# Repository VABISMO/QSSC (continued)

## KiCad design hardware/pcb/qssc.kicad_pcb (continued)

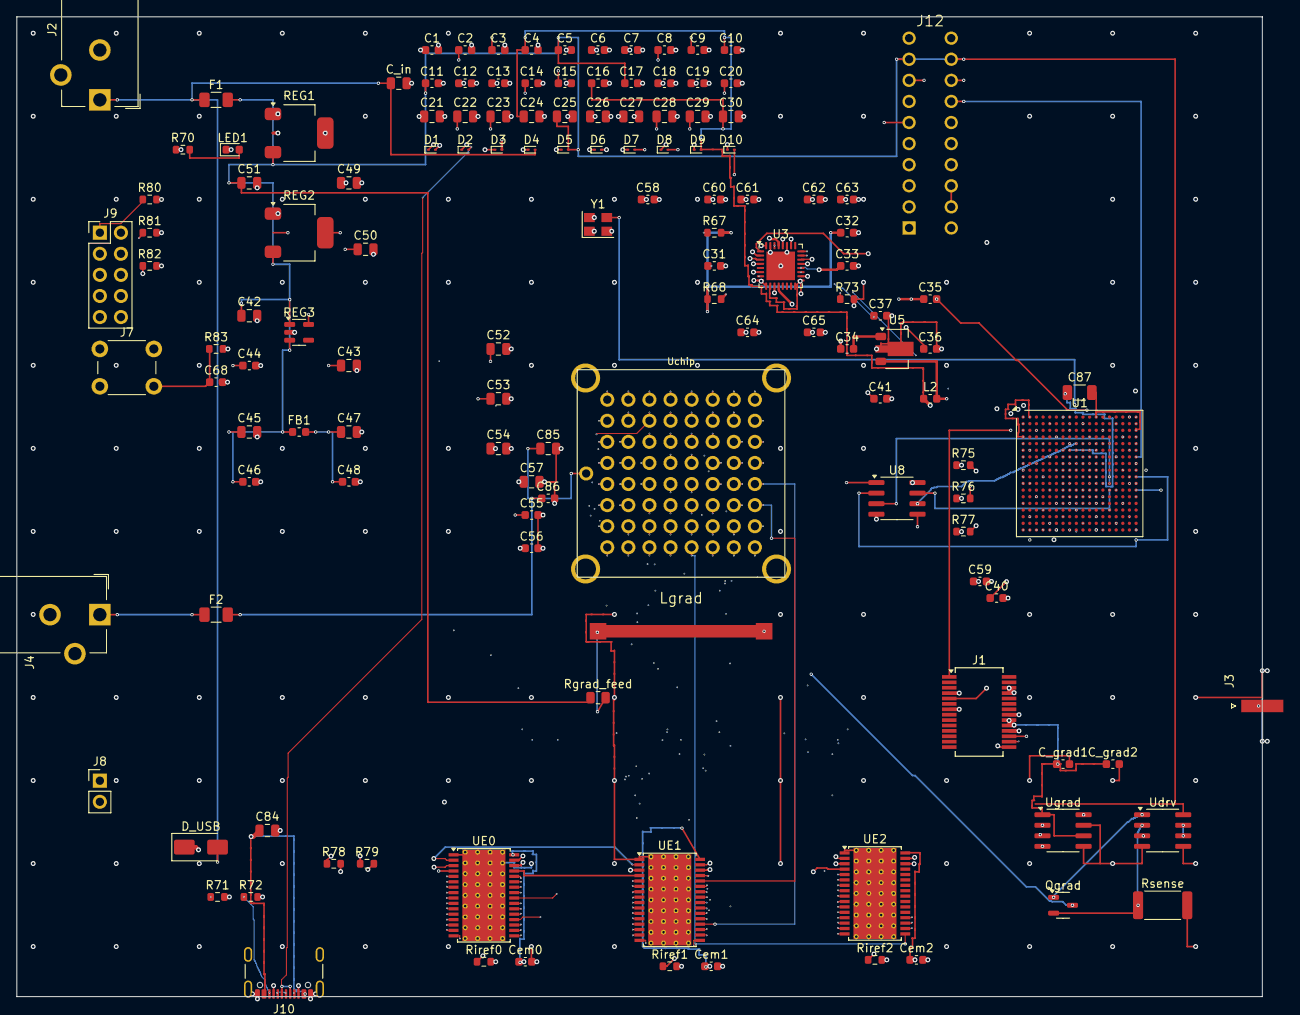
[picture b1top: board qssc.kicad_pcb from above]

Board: 6 copper layers, 150.0 x 118.0 mm, 135 parts (0 on the bottom side), 144 nets.

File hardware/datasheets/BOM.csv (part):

Board,Designators,Qty,Value,Footprint,Manufacturer,MPN,DatasheetURL
main,"C36, C37, C41",3,100n,Capacitor_SMD:C_0603_1608Metric,,,
grad,"C36, C37, C41",3,100n,Capacitor_SMD:C_0603_1608Metric,,,
main,"C1, C2, C3, C4, C5, C6, C7, C8, C9, C10, C11, C12, C13, C14, C15, C16, C17, C18, C19, C20, C40, C44, C46, C48, C55, C56, C58, C59, C60, C61, C62, C63, C64, C65, C68, C86, Cem0, Cem1, Cem2",39,100nF,Capacitor_SMD:C_0603_1608Metric,,,
grad,"C_grad1, C_grad2, C1, C2, C3, C4, C5, C6, C7, C8, C9, C10, C11, C12, C13, C14, C15, C16, C17, C18, C19, C20, C40, C44, C46, C48, C55, C56, C58, C59, C60, C61, C62, C63, C64, C65, C68, C86, Cem0, Cem1, Cem2",41,100nF,Capacitor_SMD:C_0603_1608Metric,,,
main,L2,1,100nH,Inductor_SMD:L_0603_1608Metric,,,
grad,L2,1,100nH,Inductor_SMD:L_0603_1608Metric,,,
main,"C34, C35",2,100p,Capacitor_SMD:C_0603_1608Metric,,,
grad,"C34, C35",2,100p,Capacitor_SMD:C_0603_1608Metric,,,
main,R83,1,10k,Resistor_SMD:R_0603_1608Metric,,,
grad,R83,1,10k,Resistor_SMD:R_0603_1608Metric,,,
main,C32,1,10n,Capacitor_SMD:C_0603_1608Metric,,,
grad,C32,1,10n,Capacitor_SMD:C_0603_1608Metric,,,
main,R67,1,1k,Resistor_SMD:R_0603_1608Metric,,,
grad,R67,1,1k,Resistor_SMD:R_0603_1608Metric,,,
main,R68,1,2.2k,Resistor_SMD:R_0603_1608Metric,,,
grad,R68,1,2.2k,Resistor_SMD:R_0603_1608Metric,,,
main,"C31, C33",2,220p,Capacitor_SMD:C_0603_1608Metric,,,
grad,"C31, C33",2,220p,Capacitor_SMD:C_0603_1608Metric,,,
main,"C49, C50, C85",3,22uF,Capacitor_SMD:C_0805_2012Metric,,,
grad,"C49, C50, C85",3,22uF,Capacitor_SMD:C_0805_2012Metric,,,
main,"R78, R79",2,27R,Resistor_SMD:R_0603_1608Metric,,,
grad,"R78, R79",2,27R,Resistor_SMD:R_0603_1608Metric,,,
main,R70,1,330,Resistor_SMD:R_0603_1608Metric,,,
grad,R70,1,330,Resistor_SMD:R_0603_1608Metric,,,
main,"R73, R75, R76, R77, R80, R81, R82",7,4.7k,Resistor_SMD:R_0603_1608Metric,,,
grad,"R73, R75, R76, R77, R80, R81, R82",7,4.7k,Resistor_SMD:R_0603_1608Metric,,,
main,"C52, C53, C54, C57, C84",5,4.7uF,Capacitor_SMD:C_0805_2012Metric,,,
grad,"C52, C53, C54, C57, C84",5,4.7uF,Capacitor_SMD:C_0805_2012Metric,,,
main,C87,1,47uF,Capacitor_SMD:C_1206_3216Metric,,,
grad,C87,1,47uF,Capacitor_SMD:C_1206_3216Metric,,,
main,"R71, R72",2,5.1k,Resistor_SMD:R_0603_1608Metric,,,
grad,"R71, R72",2,5.1k,Resistor_SMD:R_0603_1608Metric,,,
main,"D1, D2, D3, D4, D5, D6, D7, D8, D9, D10",10,ESD5V0,Diode_SMD:D_SOD-923,ON Semi,ESD5V0S3B-U,https://www.onsemi.com/pub/Collateral/ESD5V0S3B-U-D.PDF
grad,"D1, D2, D3, D4, D5, D6, D7, D8, D9, D10",10,ESD5V0,Diode_SMD:D_SOD-923,ON Semi,ESD5V0S3B-U,https://www.onsemi.com/pub/Collateral/ESD5V0S3B-U-D.PDF
grad,Rgrad_feed,1,0R,Resistor_SMD:R_0805_2012Metric,,,
grad,Rsense,1,1,Resistor_SMD:R_2512_6332Metric,,,
main,Y1,1,100MHz XO,Oscillator:Oscillator_SMD_Abracon_ASE-4Pin_3.2x2.5mm,Abracon,ASE-100.000MHZ-LR,https://abracon.com/Oscillators/ASE.pdf
grad,Y1,1,100MHz XO,Oscillator:Oscillator_SMD_Abracon_ASE-4Pin_3.2x2.5mm,Abracon,ASE-100.000MHZ-LR,https://abracon.com/Oscillators/ASE.pdf
head,"C_ahf, Cref, Crio0, Crio1, Crio2, Crio3, Cua0, Cua1, Cua2, Cua3, Cud0, Cud1, Cud2, Cud3, Cur0, Cur1, Cur2, Cur3, Cut0, Cut1, Cut2, Cut3, Cut4, Cut5, Cut6, Cut7, Cut8, Cut9, Cut10, Cut11, Cut12, Cut13, Cut14, Cut15",34,100nF,Capacitor_SMD:C_0603_1608Metric,,,
head,"Rref1, Rref2",2,10k,Resistor_SMD:R_0603_1608Metric,,,
main,"C_in, C21, C22, C23, C24, C25, C26, C27, C28, C29, C30, C42, C43, C45, C47, C51",16,10uF,Capacitor_SMD:C_0805_2012Metric,,,
head,"C_5V, C_Abulk, CuaB0, CuaB1, CuaB2, CuaB3",6,10uF,Capacitor_SMD:C_0805_2012Metric,,,
grad,"C_in, C21, C22, C23, C24, C25, C26, C27, C28, C29, C30, C42, C43, C45, C47, C51",16,10uF,Capacitor_SMD:C_0805_2012Metric,,,
main,J4,1,12V LED,Connector_BarrelJack:BarrelJack_CUI_PJ-102AH_Horizontal,CUI,PJ-102AH,https://www.cui.com/product/resource/pj-102a.pdf
grad,J4,1,12V LED,Connector_BarrelJack:BarrelJack_CUI_PJ-102AH_Horizontal,CUI,PJ-102AH,https://www.cui.com/product/resource/pj-102a.pdf
main,F2,1,1A PTC,Fuse:Fuse_1206_3216Metric,,,
grad,F2,1,1A PTC,Fuse:Fuse_1206_3216Metric,,,
head,"Rf0, Rf1, Rf2, Rf3, Rf4, Rf5, Rf6, Rf7, Rf8, Rf9, Rf10, Rf11, Rf12, Rf13, Rf14, Rf15, Rf16, Rf17, Rf18, Rf19, Rf20, Rf21, Rf22, Rf23, Rf24, Rf25, Rf26, Rf27, Rf28, Rf29, Rf30, Rf31, Rf32, Rf33, Rf34, Rf35, Rf36, Rf37, Rf38, Rf39, Rf40, Rf41, Rf42, Rf43, Rf44, Rf45, Rf46, Rf47, Rf48, Rf49, Rf50, Rf51, Rf52, Rf53, Rf54, Rf55, Rf56, Rf57, Rf58, Rf59, Rf60, Rf61, Rf62, Rf63",64,1M,Resistor_SMD:R_0603_1608Metric,,,
head,"Cf0, Cf1, Cf2, Cf3, Cf4, Cf5, Cf6, Cf7, Cf8, Cf9, Cf10, Cf11, Cf12, Cf13, Cf14, Cf15, Cf16, Cf17, Cf18, Cf19, Cf20, Cf21, Cf22, Cf23, Cf24, Cf25, Cf26, Cf27, Cf28, Cf29, Cf30, Cf31, Cf32, Cf33, Cf34, Cf35, Cf36, Cf37, Cf38, Cf39, Cf40, Cf41, Cf42, Cf43, Cf44, Cf45, Cf46, Cf47, Cf48, Cf49, Cf50, Cf51, Cf52, Cf53, Cf54, Cf55, Cf56, Cf57, Cf58, Cf59, Cf60, Cf61, Cf62, Cf63",64,1pF,Capacitor_SMD:C_0603_1608Metric,,,
head,"Crgc0, Crgc1, Crgc2, Crgc3, Crgd0, Crgd1, Crgd2, Crgd3",8,1uF,Capacitor_SMD:C_0603_1608Metric,,,
main,F1,1,2A PTC,Fuse:Fuse_1206_3216Metric,Littelfuse,nanoSMDC020F,https://www.littelfuse.com/media?resourcetype=datasheets&val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
grad,F1,1,2A PTC,Fuse:Fuse_1206_3216Metric,Littelfuse,nanoSMDC020F,https://www.littelfuse.com/media?resourcetype=datasheets&val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
main,"Riref0, Riref1, Riref2",3,4.87k,Resistor_SMD:R_0603_1608Metric,,,
grad,"Riref0, Riref1, Riref2",3,4.87k,Resistor_SMD:R_0603_1608Metric,,,
main,J2,1,5V Barrel,Connector_BarrelJack:BarrelJack_CUI_PJ-102AH_Horizontal,CUI,PJ-102AH,https://www.cui.com/product/resource/pj-102a.pdf
grad,J2,1,5V Barrel,Connector_BarrelJack:BarrelJack_CUI_PJ-102AH_Horizontal,CUI,PJ-102AH,https://www.cui.com/product/resource/pj-102a.pdf
main,FB1,1,600Ω@100MHz,Inductor_SMD:L_0603_1608Metric,Murata,BLM18AG601SN1D,https://www.murata.com/products/productdata/8796738650146/EN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
head,FB_A,1,600Ω@100MHz,Inductor_SMD:L_0603_1608Metric,Murata,BLM18AG601SN1D,https://www.murata.com/products/productdata/8796738650146/EN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
grad,FB1,1,600Ω@100MHz,Inductor_SMD:L_0603_1608Metric,Murata,BLM18AG601SN1D,https://www.murata.com/products/productdata/8796738650146/EN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
head,"UAD0, UAD1, UAD2, UAD3",4,AD7616,Package_QFP:LQFP-80_14x14mm_P0.65mm,Analog Devices,AD7616BSTZ,https://www.analog.com/media/en/technical-documentation/data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
main,U3,1,ADF4351BCPZ,Package_DFN_QFN:QFN-32-1EP_5x5mm_P0.5mm_EP3.45x3.45mm,Analog Devices,ADF4351BCPZ,https://www.analog.com/media/en/technical-documentation/data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
grad,U3,1,ADF4351BCPZ,Package_DFN_QFN:QFN-32-1EP_5x5mm_P0.5mm_EP3.45x3.45mm,Analog Devices,ADF4351BCPZ,https://www.analog.com/media/en/technical-documentation/data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
main,REG2,1,AMS1117-1.8,Package_TO_SOT_SMD:SOT-223-3_TabPin2,AMS,AMS1117-1.8,https://www.mouser.com/datasheet/2/260/AMS1117-Datasheet-127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
grad,REG2,1,AMS1117-1.8,Package_TO_SOT_SMD:SOT-223-3_TabPin2,AMS,AMS1117-1.8,https://www.mouser.com/datasheet/2/260/AMS1117-Datasheet-127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
main,REG1,1,AMS1117-3.3,Package_TO_SOT_SMD:SOT-223-3_TabPin2,AMS,AMS1117-3.3,https://www.mouser.com/datasheet/2/260/AMS1117-Datasheet-127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
grad,REG1,1,AMS1117-3.3,Package_TO_SOT_SMD:SOT-223-3_TabPin2,AMS,AMS1117-3.3,https://www.mouser.com/datasheet/2/260/AMS1117-Datasheet-127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
main,REG3,1,AP2127K-1.0,Package_TO_SOT_SMD:SOT-23-5,Diodes Inc,AP2127K-1.0,https://www.diodes.com/assets/Datasheets/AP2127K.pdf
grad,REG3,1,AP2127K-1.0,Package_TO_SOT_SMD:SOT-23-5,Diodes Inc,AP2127K-1.0,https://www.diodes.com/assets/Datasheets/AP2127K.pdf
head,J12,1,BTB_DAUGHTER,qssc:Conn_02x10_BTB,Würth Elektronik,61002021121,https://www.we-online.com/en/components/products/WR-PHD_2_54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
main,J12,1,BTB_HOST,qssc:Conn_02x10_BTB,Würth Elektronik,61302011121,https://www.we-online.com/en/components/products/WR-PHD_2_54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
grad,J12,1,BTB_HOST,qssc:Conn_02x10_BTB,Würth Elektronik,61302011121,https://www.we-online.com/en/components/products/WR-PHD_2_54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
head,Uchip,1,ChipSocket_2.54_DET,qssc:ChipSocket_2.54_DET,,,
main,Uchip,1,ChipSocket_2.54_EM,qssc:ChipSocket_2.54_EM,,,
grad,Uchip,1,ChipSocket_2.54_EM,qssc:ChipSocket_2.54_EM,,,
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
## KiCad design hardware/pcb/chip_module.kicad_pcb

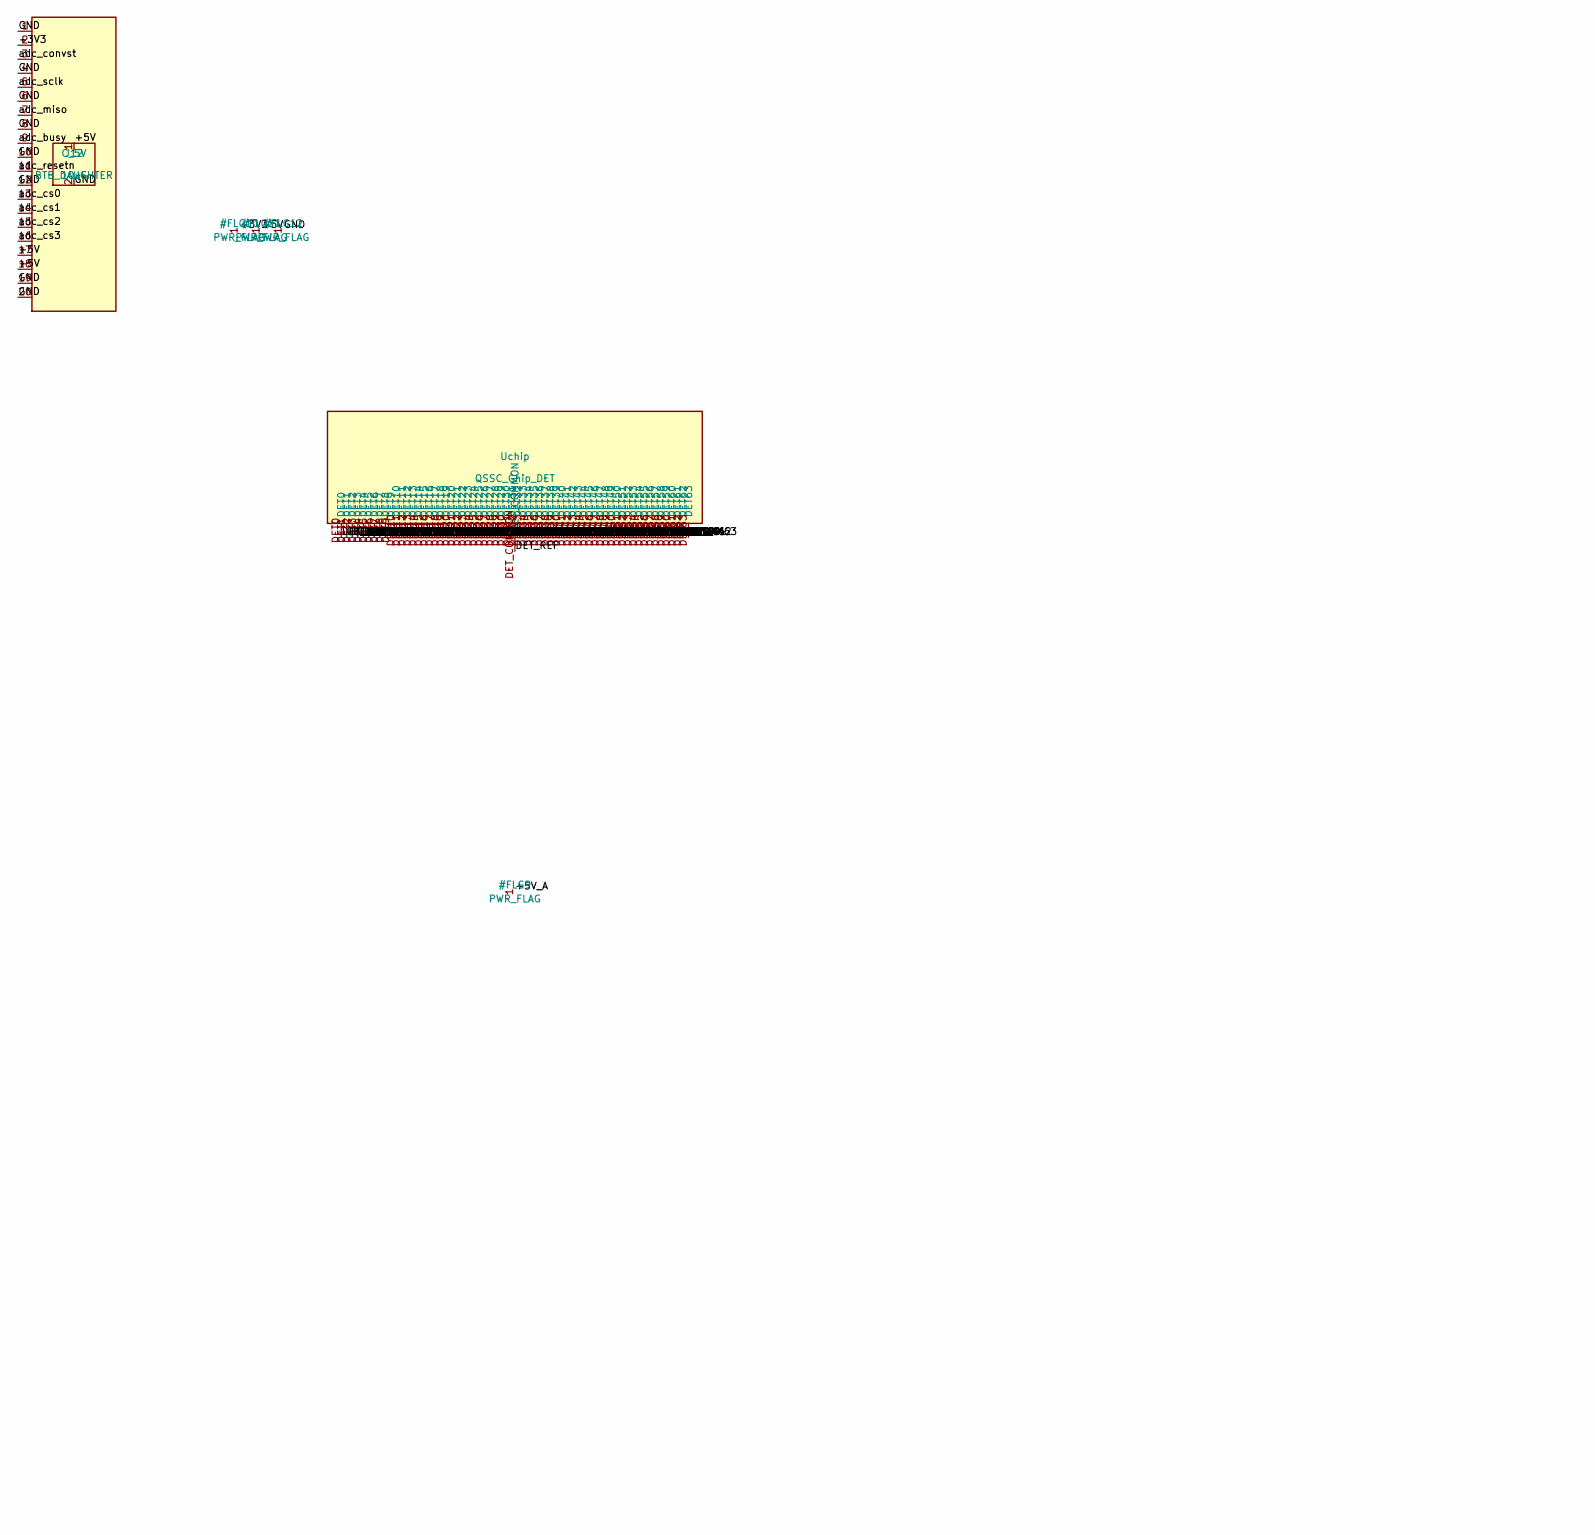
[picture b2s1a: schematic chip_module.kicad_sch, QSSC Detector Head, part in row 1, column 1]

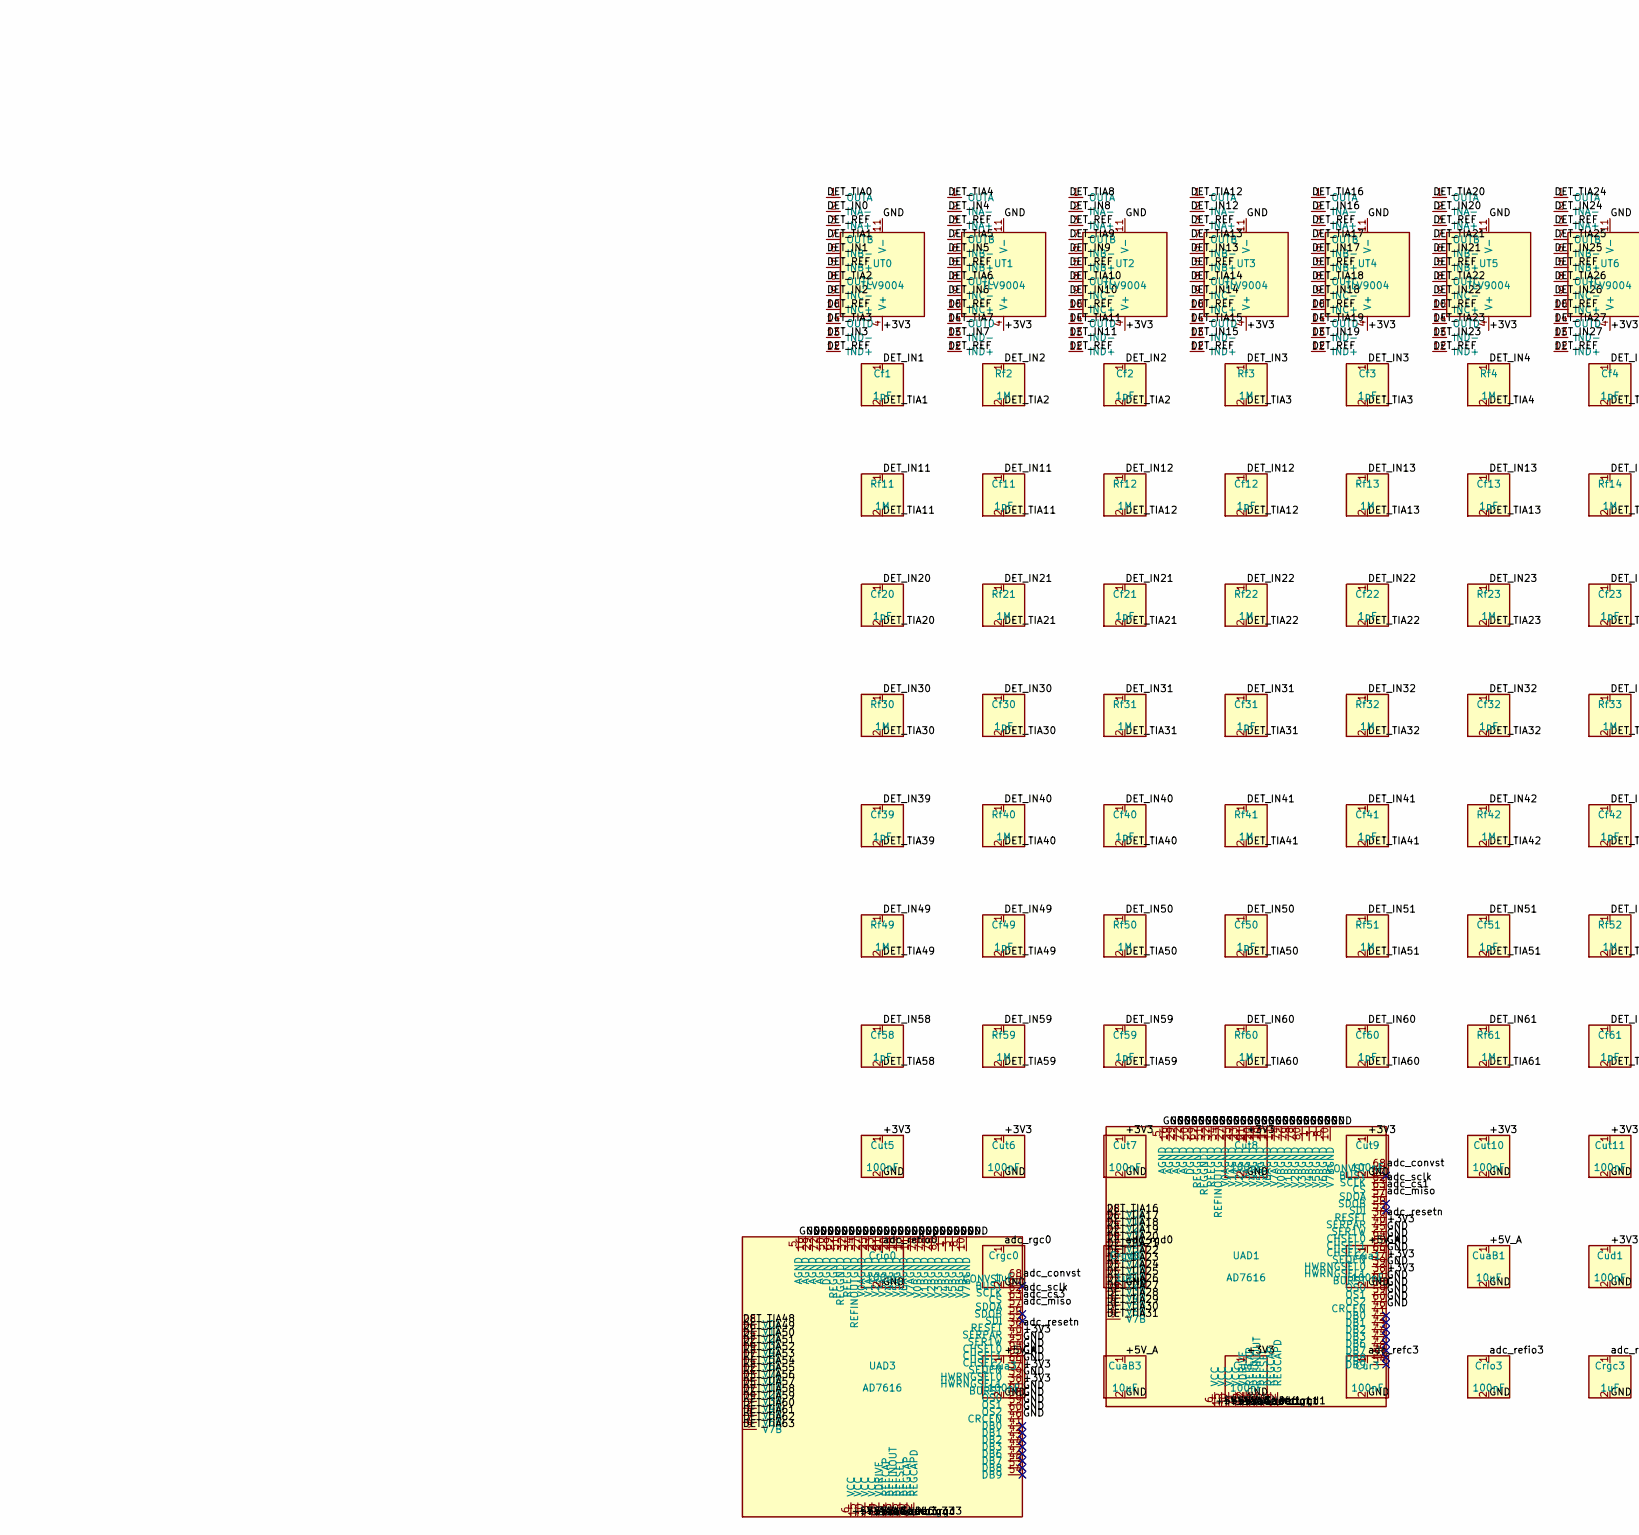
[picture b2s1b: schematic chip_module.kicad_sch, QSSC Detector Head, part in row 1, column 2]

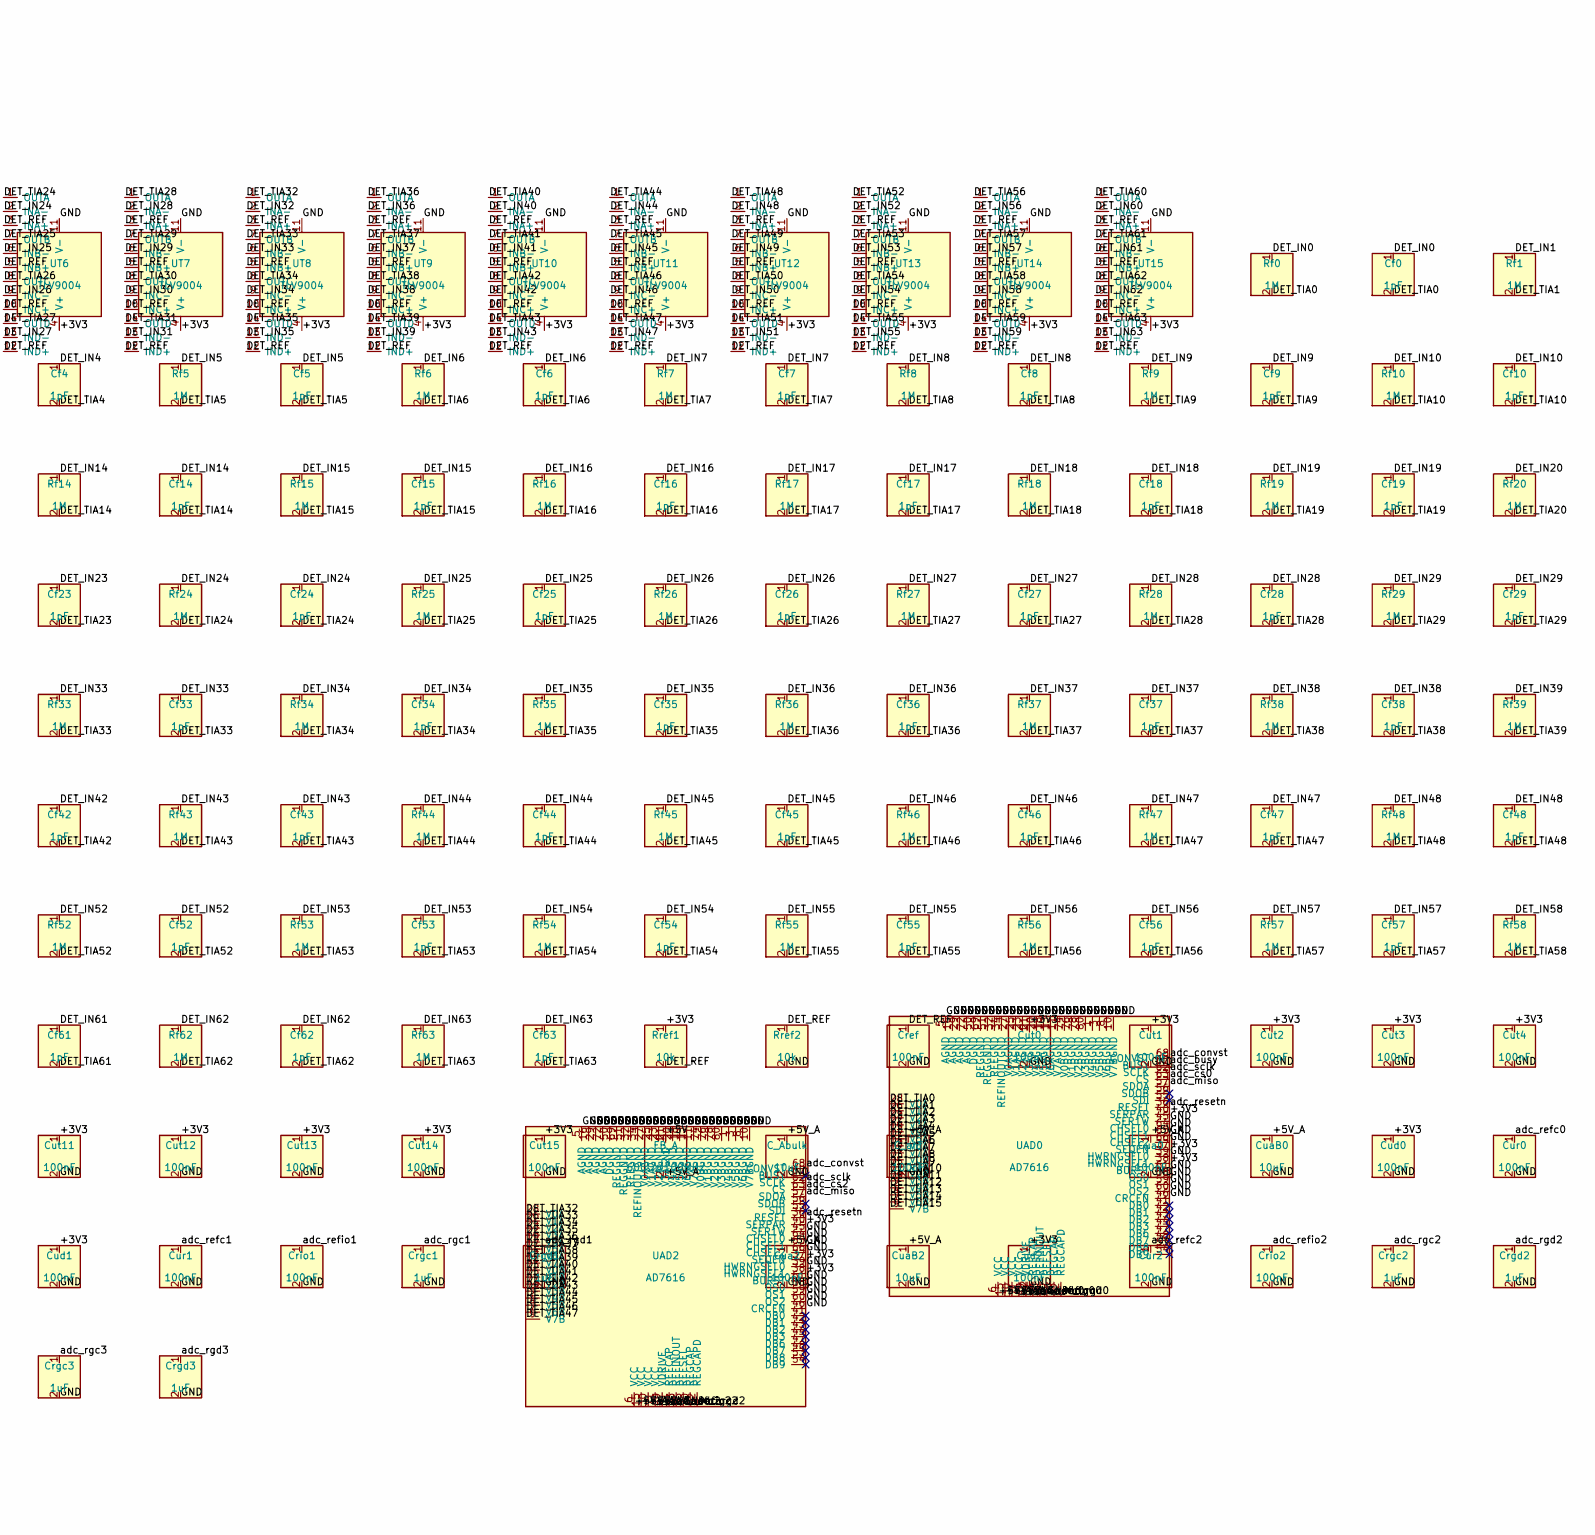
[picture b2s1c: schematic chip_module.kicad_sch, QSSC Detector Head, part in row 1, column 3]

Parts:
C_5V: 10uF; C_0805_2012Metric
C_Abulk: 10uF; C_0805_2012Metric
C_ahf: 100nF; C_0603_1608Metric
Cf0, Cf1, Cf2, Cf3, Cf4, Cf5, Cf6, Cf7, Cf8, Cf9, Cf10, Cf11, Cf12, Cf13, Cf14, Cf15, Cf16, Cf17, Cf18, Cf19, Cf20, Cf21, Cf22, Cf23, Cf24, Cf25, Cf26, Cf27, Cf28, Cf29, Cf30, Cf31, Cf32, Cf33, Cf34, Cf35, Cf36, Cf37, Cf38, Cf39, Cf40, Cf41, Cf42, Cf43, Cf44, Cf45, Cf46, Cf47, Cf48, Cf49, Cf50, Cf51, Cf52, Cf53, Cf54, Cf55, Cf56, Cf57, Cf58, Cf59, Cf60, Cf61, Cf62, Cf63: 1pF; C_0603_1608Metric
Cref: 100nF; C_0603_1608Metric
Crgc0, Crgc1, Crgc2, Crgc3: 1uF; C_0603_1608Metric
Crgd0, Crgd1, Crgd2, Crgd3: 1uF; C_0603_1608Metric
Crio0, Crio1, Crio2, Crio3: 100nF; C_0603_1608Metric
Cua0, Cua1, Cua2, Cua3: 100nF; C_0603_1608Metric
CuaB0, CuaB1, CuaB2, CuaB3: 10uF; C_0805_2012Metric
Cud0, Cud1, Cud2, Cud3: 100nF; C_0603_1608Metric
Cur0, Cur1, Cur2, Cur3: 100nF; C_0603_1608Metric
Cut0, Cut1, Cut2, Cut3, Cut4, Cut5, Cut6, Cut7, Cut8, Cut9, Cut10, Cut11, Cut12, Cut13, Cut14, Cut15: 100nF; C_0603_1608Metric
FB_A: 600Ω@100MHz; L_0603_1608Metric
J12: BTB_DAUGHTER; Conn_02x10_BTB
Rf0, Rf1, Rf2, Rf3, Rf4, Rf5, Rf6, Rf7, Rf8, Rf9, Rf10, Rf11, Rf12, Rf13, Rf14, Rf15, Rf16, Rf17, Rf18, Rf19, Rf20, Rf21, Rf22, Rf23, Rf24, Rf25, Rf26, Rf27, Rf28, Rf29, Rf30, Rf31, Rf32, Rf33, Rf34, Rf35, Rf36, Rf37, Rf38, Rf39, Rf40, Rf41, Rf42, Rf43, Rf44, Rf45, Rf46, Rf47, Rf48, Rf49, Rf50, Rf51, Rf52, Rf53, Rf54, Rf55, Rf56, Rf57, Rf58, Rf59, Rf60, Rf61, Rf62, Rf63: 1M; R_0603_1608Metric
Rref1, Rref2: 10k; R_0603_1608Metric
UAD0, UAD1, UAD2, UAD3: AD7616; LQFP-80_14x14mm_P0.65mm
UT0, UT1, UT2, UT3, UT4, UT5, UT6, UT7, UT8, UT9, UT10, UT11, UT12, UT13, UT14, UT15: TLV9004; TSSOP-14_4.4x5mm_P0.65mm
Uchip: QSSC_Chip_DET

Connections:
+3V3: Cud0.1, Cud1.1, Cud2.1, Cud3.1, Cut0.1, Cut1.1, Cut2.1, Cut3.1, Cut4.1, Cut5.1, Cut6.1, Cut7.1, Cut8.1, Cut9.1, Cut10.1, Cut11.1, Cut12.1, Cut13.1, Cut14.1, Cut15.1, J12.2, Rref1.1, UAD0.37 (SEQEN), UAD0.38 (HWRNGSEL1), UAD0.40 (SERPAR), UAD0.49 (VDRIVE), UAD1.37 (SEQEN), UAD1.38 (HWRNGSEL1), UAD1.40 (SERPAR), UAD1.49 (VDRIVE), UAD2.37 (SEQEN), UAD2.38 (HWRNGSEL1), UAD2.40 (SERPAR), UAD2.49 (VDRIVE), UAD3.37 (SEQEN), UAD3.38 (HWRNGSEL1), UAD3.40 (SERPAR), UAD3.49 (VDRIVE), UT0.4 (V+), UT1.4 (V+), UT2.4 (V+), UT3.4 (V+), UT4.4 (V+), UT5.4 (V+), UT6.4 (V+), UT7.4 (V+), UT8.4 (V+), UT9.4 (V+), UT10.4 (V+), UT11.4 (V+), UT12.4 (V+), UT13.4 (V+), UT14.4 (V+), UT15.4 (V+)
+5V: C_5V.1, FB_A.1, J12.17, J12.18
+5V_A: C_Abulk.1, C_ahf.1, Cua0.1, Cua1.1, Cua2.1, Cua3.1, CuaB0.1, CuaB1.1, CuaB2.1, CuaB3.1, FB_A.2, UAD0.6 (VCC), UAD0.15 (VCC), UAD0.30 (VCC), UAD0.71 (VCC), UAD1.6 (VCC), UAD1.15 (VCC), UAD1.30 (VCC), UAD1.71 (VCC), UAD2.6 (VCC), UAD2.15 (VCC), UAD2.30 (VCC), UAD2.71 (VCC), UAD3.6 (VCC), UAD3.15 (VCC), UAD3.30 (VCC), UAD3.71 (VCC)
DET_IN0: Cf0.1, Rf0.1, UT0.2 (INA-), Uchip.DET0
DET_IN1: Cf1.1, Rf1.1, UT0.6 (INB-), Uchip.DET1
DET_IN2: Cf2.1, Rf2.1, UT0.9 (INC-), Uchip.DET2
DET_IN3: Cf3.1, Rf3.1, UT0.13 (IND-), Uchip.DET3
DET_IN4: Cf4.1, Rf4.1, UT1.2 (INA-), Uchip.DET4
DET_IN5: Cf5.1, Rf5.1, UT1.6 (INB-), Uchip.DET5
DET_IN6: Cf6.1, Rf6.1, UT1.9 (INC-), Uchip.DET6
DET_IN7: Cf7.1, Rf7.1, UT1.13 (IND-), Uchip.DET7
DET_IN8: Cf8.1, Rf8.1, UT2.2 (INA-), Uchip.DET8
DET_IN9: Cf9.1, Rf9.1, UT2.6 (INB-), Uchip.DET9
DET_IN10: Cf10.1, Rf10.1, UT2.9 (INC-), Uchip.DET10
DET_IN11: Cf11.1, Rf11.1, UT2.13 (IND-), Uchip.DET11
DET_IN12: Cf12.1, Rf12.1, UT3.2 (INA-), Uchip.DET12
DET_IN13: Cf13.1, Rf13.1, UT3.6 (INB-), Uchip.DET13
DET_IN14: Cf14.1, Rf14.1, UT3.9 (INC-), Uchip.DET14
DET_IN15: Cf15.1, Rf15.1, UT3.13 (IND-), Uchip.DET15
DET_IN16: Cf16.1, Rf16.1, UT4.2 (INA-), Uchip.DET16
DET_IN17: Cf17.1, Rf17.1, UT4.6 (INB-), Uchip.DET17
DET_IN18: Cf18.1, Rf18.1, UT4.9 (INC-), Uchip.DET18
DET_IN19: Cf19.1, Rf19.1, UT4.13 (IND-), Uchip.DET19
DET_IN20: Cf20.1, Rf20.1, UT5.2 (INA-), Uchip.DET20
DET_IN21: Cf21.1, Rf21.1, UT5.6 (INB-), Uchip.DET21
DET_IN22: Cf22.1, Rf22.1, UT5.9 (INC-), Uchip.DET22
DET_IN23: Cf23.1, Rf23.1, UT5.13 (IND-), Uchip.DET23
DET_IN24: Cf24.1, Rf24.1, UT6.2 (INA-), Uchip.DET24
DET_IN25: Cf25.1, Rf25.1, UT6.6 (INB-), Uchip.DET25
DET_IN26: Cf26.1, Rf26.1, UT6.9 (INC-), Uchip.DET26
DET_IN27: Cf27.1, Rf27.1, UT6.13 (IND-), Uchip.DET27
DET_IN28: Cf28.1, Rf28.1, UT7.2 (INA-), Uchip.DET28
DET_IN29: Cf29.1, Rf29.1, UT7.6 (INB-), Uchip.DET29
DET_IN30: Cf30.1, Rf30.1, UT7.9 (INC-), Uchip.DET30
DET_IN31: Cf31.1, Rf31.1, UT7.13 (IND-), Uchip.DET31
DET_IN32: Cf32.1, Rf32.1, UT8.2 (INA-), Uchip.DET32
DET_IN33: Cf33.1, Rf33.1, UT8.6 (INB-), Uchip.DET33
DET_IN34: Cf34.1, Rf34.1, UT8.9 (INC-), Uchip.DET34
DET_IN35: Cf35.1, Rf35.1, UT8.13 (IND-), Uchip.DET35
DET_IN36: Cf36.1, Rf36.1, UT9.2 (INA-), Uchip.DET36
DET_IN37: Cf37.1, Rf37.1, UT9.6 (INB-), Uchip.DET37
DET_IN38: Cf38.1, Rf38.1, UT9.9 (INC-), Uchip.DET38
DET_IN39: Cf39.1, Rf39.1, UT9.13 (IND-), Uchip.DET39
DET_IN40: Cf40.1, Rf40.1, UT10.2 (INA-), Uchip.DET40
DET_IN41: Cf41.1, Rf41.1, UT10.6 (INB-), Uchip.DET41
DET_IN42: Cf42.1, Rf42.1, UT10.9 (INC-), Uchip.DET42
DET_IN43: Cf43.1, Rf43.1, UT10.13 (IND-), Uchip.DET43
DET_IN44: Cf44.1, Rf44.1, UT11.2 (INA-), Uchip.DET44
DET_IN45: Cf45.1, Rf45.1, UT11.6 (INB-), Uchip.DET45
DET_IN46: Cf46.1, Rf46.1, UT11.9 (INC-), Uchip.DET46
DET_IN47: Cf47.1, Rf47.1, UT11.13 (IND-), Uchip.DET47
DET_IN48: Cf48.1, Rf48.1, UT12.2 (INA-), Uchip.DET48
DET_IN49: Cf49.1, Rf49.1, UT12.6 (INB-), Uchip.DET49
DET_IN50: Cf50.1, Rf50.1, UT12.9 (INC-), Uchip.DET50
DET_IN51: Cf51.1, Rf51.1, UT12.13 (IND-), Uchip.DET51
DET_IN52: Cf52.1, Rf52.1, UT13.2 (INA-), Uchip.DET52
DET_IN53: Cf53.1, Rf53.1, UT13.6 (INB-), Uchip.DET53
DET_IN54: Cf54.1, Rf54.1, UT13.9 (INC-), Uchip.DET54
DET_IN55: Cf55.1, Rf55.1, UT13.13 (IND-), Uchip.DET55
DET_IN56: Cf56.1, Rf56.1, UT14.2 (INA-), Uchip.DET56
DET_IN57: Cf57.1, Rf57.1, UT14.6 (INB-), Uchip.DET57
DET_IN58: Cf58.1, Rf58.1, UT14.9 (INC-), Uchip.DET58
DET_IN59: Cf59.1, Rf59.1, UT14.13 (IND-), Uchip.DET59
DET_IN60: Cf60.1, Rf60.1, UT15.2 (INA-), Uchip.DET60
DET_IN61: Cf61.1, Rf61.1, UT15.6 (INB-), Uchip.DET61
DET_IN62: Cf62.1, Rf62.1, UT15.9 (INC-), Uchip.DET62
DET_IN63: Cf63.1, Rf63.1, UT15.13 (IND-), Uchip.DET63
DET_REF: Cref.1, Rref1.2, Rref2.1, UT0.3 (INA+), UT0.5 (INB+), UT0.10 (INC+), UT0.12 (IND+), UT1.3 (INA+), UT1.5 (INB+), UT1.10 (INC+), UT1.12 (IND+), UT2.3 (INA+), UT2.5 (INB+), UT2.10 (INC+), UT2.12 (IND+), UT3.3 (INA+), UT3.5 (INB+), UT3.10 (INC+), UT3.12 (IND+), UT4.3 (INA+), UT4.5 (INB+), UT4.10 (INC+), UT4.12 (IND+), UT5.3 (INA+), UT5.5 (INB+), UT5.10 (INC+), UT5.12 (IND+), UT6.3 (INA+), UT6.5 (INB+), UT6.10 (INC+), UT6.12 (IND+), UT7.3 (INA+), UT7.5 (INB+), UT7.10 (INC+), UT7.12 (IND+), UT8.3 (INA+), UT8.5 (INB+), UT8.10 (INC+), UT8.12 (IND+), UT9.3 (INA+), UT9.5 (INB+), UT9.10 (INC+), UT9.12 (IND+), UT10.3 (INA+), UT10.5 (INB+), UT10.10 (INC+), UT10.12 (IND+), UT11.3 (INA+), UT11.5 (INB+), UT11.10 (INC+), UT11.12 (IND+), UT12.3 (INA+), UT12.5 (INB+), UT12.10 (INC+), UT12.12 (IND+), UT13.3 (INA+), UT13.5 (INB+), UT13.10 (INC+), UT13.12 (IND+), UT14.3 (INA+), UT14.5 (INB+), UT14.10 (INC+), UT14.12 (IND+), UT15.3 (INA+), UT15.5 (INB+), UT15.10 (INC+), UT15.12 (IND+), Uchip.DET_COMMON
DET_TIA0: Cf0.2, Rf0.2, UAD0.28 (V0A), UT0.1 (OUTA)
DET_TIA1: Cf1.2, Rf1.2, UAD0.26 (V1A), UT0.7 (OUTB)
DET_TIA2: Cf2.2, Rf2.2, UAD0.24 (V2A), UT0.8 (OUTC)
DET_TIA3: Cf3.2, Rf3.2, UAD0.22 (V3A), UT0.14 (OUTD)
DET_TIA4: Cf4.2, Rf4.2, UAD0.19 (V4A), UT1.1 (OUTA)
DET_TIA5: Cf5.2, Rf5.2, UAD0.17 (V5A), UT1.7 (OUTB)
DET_TIA6: Cf6.2, Rf6.2, UAD0.14 (V6A), UT1.8 (OUTC)
DET_TIA7: Cf7.2, Rf7.2, UAD0.12 (V7A), UT1.14 (OUTD)
DET_TIA8: Cf8.2, Rf8.2, UAD0.73 (V0B), UT2.1 (OUTA)
DET_TIA9: Cf9.2, Rf9.2, UAD0.75 (V1B), UT2.7 (OUTB)
DET_TIA10: Cf10.2, Rf10.2, UAD0.77 (V2B), UT2.8 (OUTC)
DET_TIA11: Cf11.2, Rf11.2, UAD0.79 (V3B), UT2.14 (OUTD)
DET_TIA12: Cf12.2, Rf12.2, UAD0.2 (V4B), UT3.1 (OUTA)
DET_TIA13: Cf13.2, Rf13.2, UAD0.4 (V5B), UT3.7 (OUTB)
DET_TIA14: Cf14.2, Rf14.2, UAD0.7 (V6B), UT3.8 (OUTC)
DET_TIA15: Cf15.2, Rf15.2, UAD0.9 (V7B), UT3.14 (OUTD)
DET_TIA16: Cf16.2, Rf16.2, UAD1.28 (V0A), UT4.1 (OUTA)
DET_TIA17: Cf17.2, Rf17.2, UAD1.26 (V1A), UT4.7 (OUTB)
DET_TIA18: Cf18.2, Rf18.2, UAD1.24 (V2A), UT4.8 (OUTC)
DET_TIA19: Cf19.2, Rf19.2, UAD1.22 (V3A), UT4.14 (OUTD)
DET_TIA20: Cf20.2, Rf20.2, UAD1.19 (V4A), UT5.1 (OUTA)
DET_TIA21: Cf21.2, Rf21.2, UAD1.17 (V5A), UT5.7 (OUTB)
DET_TIA22: Cf22.2, Rf22.2, UAD1.14 (V6A), UT5.8 (OUTC)
DET_TIA23: Cf23.2, Rf23.2, UAD1.12 (V7A), UT5.14 (OUTD)
DET_TIA24: Cf24.2, Rf24.2, UAD1.73 (V0B), UT6.1 (OUTA)
DET_TIA25: Cf25.2, Rf25.2, UAD1.75 (V1B), UT6.7 (OUTB)
DET_TIA26: Cf26.2, Rf26.2, UAD1.77 (V2B), UT6.8 (OUTC)
DET_TIA27: Cf27.2, Rf27.2, UAD1.79 (V3B), UT6.14 (OUTD)
DET_TIA28: Cf28.2, Rf28.2, UAD1.2 (V4B), UT7.1 (OUTA)
DET_TIA29: Cf29.2, Rf29.2, UAD1.4 (V5B), UT7.7 (OUTB)
DET_TIA30: Cf30.2, Rf30.2, UAD1.7 (V6B), UT7.8 (OUTC)
DET_TIA31: Cf31.2, Rf31.2, UAD1.9 (V7B), UT7.14 (OUTD)
DET_TIA32: Cf32.2, Rf32.2, UAD2.28 (V0A), UT8.1 (OUTA)
DET_TIA33: Cf33.2, Rf33.2, UAD2.26 (V1A), UT8.7 (OUTB)
DET_TIA34: Cf34.2, Rf34.2, UAD2.24 (V2A), UT8.8 (OUTC)
DET_TIA35: Cf35.2, Rf35.2, UAD2.22 (V3A), UT8.14 (OUTD)
DET_TIA36: Cf36.2, Rf36.2, UAD2.19 (V4A), UT9.1 (OUTA)
DET_TIA37: Cf37.2, Rf37.2, UAD2.17 (V5A), UT9.7 (OUTB)
DET_TIA38: Cf38.2, Rf38.2, UAD2.14 (V6A), UT9.8 (OUTC)
DET_TIA39: Cf39.2, Rf39.2, UAD2.12 (V7A), UT9.14 (OUTD)
DET_TIA40: Cf40.2, Rf40.2, UAD2.73 (V0B), UT10.1 (OUTA)
DET_TIA41: Cf41.2, Rf41.2, UAD2.75 (V1B), UT10.7 (OUTB)
DET_TIA42: Cf42.2, Rf42.2, UAD2.77 (V2B), UT10.8 (OUTC)
DET_TIA43: Cf43.2, Rf43.2, UAD2.79 (V3B), UT10.14 (OUTD)
DET_TIA44: Cf44.2, Rf44.2, UAD2.2 (V4B), UT11.1 (OUTA)
DET_TIA45: Cf45.2, Rf45.2, UAD2.4 (V5B), UT11.7 (OUTB)
DET_TIA46: Cf46.2, Rf46.2, UAD2.7 (V6B), UT11.8 (OUTC)
DET_TIA47: Cf47.2, Rf47.2, UAD2.9 (V7B), UT11.14 (OUTD)
DET_TIA48: Cf48.2, Rf48.2, UAD3.28 (V0A), UT12.1 (OUTA)
DET_TIA49: Cf49.2, Rf49.2, UAD3.26 (V1A), UT12.7 (OUTB)
DET_TIA50: Cf50.2, Rf50.2, UAD3.24 (V2A), UT12.8 (OUTC)
DET_TIA51: Cf51.2, Rf51.2, UAD3.22 (V3A), UT12.14 (OUTD)
DET_TIA52: Cf52.2, Rf52.2, UAD3.19 (V4A), UT13.1 (OUTA)
DET_TIA53: Cf53.2, Rf53.2, UAD3.17 (V5A), UT13.7 (OUTB)
DET_TIA54: Cf54.2, Rf54.2, UAD3.14 (V6A), UT13.8 (OUTC)
DET_TIA55: Cf55.2, Rf55.2, UAD3.12 (V7A), UT13.14 (OUTD)
DET_TIA56: Cf56.2, Rf56.2, UAD3.73 (V0B), UT14.1 (OUTA)
DET_TIA57: Cf57.2, Rf57.2, UAD3.75 (V1B), UT14.7 (OUTB)
DET_TIA58: Cf58.2, Rf58.2, UAD3.77 (V2B), UT14.8 (OUTC)
DET_TIA59: Cf59.2, Rf59.2, UAD3.79 (V3B), UT14.14 (OUTD)
DET_TIA60: Cf60.2, Rf60.2, UAD3.2 (V4B), UT15.1 (OUTA)
DET_TIA61: Cf61.2, Rf61.2, UAD3.4 (V5B), UT15.7 (OUTB)
DET_TIA62: Cf62.2, Rf62.2, UAD3.7 (V6B), UT15.8 (OUTC)
DET_TIA63: Cf63.2, Rf63.2, UAD3.9 (V7B), UT15.14 (OUTD)
GND: C_5V.2, C_Abulk.2, C_ahf.2, Cref.2, Crgc0.2, Crgc1.2, Crgc2.2, Crgc3.2, Crgd0.2, Crgd1.2, Crgd2.2, Crgd3.2, Crio0.2, Crio1.2, Crio2.2, Crio3.2, Cua0.2, Cua1.2, Cua2.2, Cua3.2, CuaB0.2, CuaB1.2, CuaB2.2, CuaB3.2, Cud0.2, Cud1.2, Cud2.2, Cud3.2, Cur0.2, Cur1.2, Cur2.2, Cur3.2, Cut0.2, Cut1.2, Cut2.2, Cut3.2, Cut4.2, Cut5.2, Cut6.2, Cut7.2, Cut8.2, Cut9.2, Cut10.2, Cut11.2, Cut12.2, Cut13.2, Cut14.2, Cut15.2, J12.1, J12.4, J12.6, J12.8, J12.10, J12.12, J12.19, J12.20, Rref2.2, UAD0.1 (V4BGND), UAD0.3 (V5BGND), UAD0.5 (AGND), UAD0.8 (V6BGND), UAD0.10 (V7BGND), UAD0.11 (V7AGND), UAD0.13 (V6AGND), UAD0.16 (AGND), UAD0.18 (V5AGND), UAD0.20 (V4AGND), UAD0.21 (V3AGND), UAD0.23 (V2AGND), UAD0.25 (V1AGND), UAD0.27 (V0AGND), UAD0.29 (AGND), UAD0.32 (REFGND), UAD0.34 (REFINOUTGND), UAD0.35 (REFSEL), UAD0.39 (HWRNGSEL0), UAD0.45 (SER1W), UAD0.46 (CRCEN), UAD0.50 (DGND), UAD0.51 (REGGNDD), UAD0.58 (OS0), UAD0.59 (OS1), UAD0.60 (OS2), UAD0.61 (BURST), UAD0.64 (CHSEL0), UAD0.65 (CHSEL1), UAD0.66 (CHSEL2), UAD0.69 (REGGND), UAD0.72 (AGND), UAD0.74 (V0BGND), UAD0.76 (V1BGND), UAD0.78 (V2BGND), UAD0.80 (V3BGND), UAD1.1 (V4BGND), UAD1.3 (V5BGND), UAD1.5 (AGND), UAD1.8 (V6BGND), UAD1.10 (V7BGND), UAD1.11 (V7AGND), UAD1.13 (V6AGND), UAD1.16 (AGND), UAD1.18 (V5AGND), UAD1.20 (V4AGND), UAD1.21 (V3AGND), UAD1.23 (V2AGND), UAD1.25 (V1AGND), UAD1.27 (V0AGND), UAD1.29 (AGND), UAD1.32 (REFGND), UAD1.34 (REFINOUTGND), UAD1.35 (REFSEL), UAD1.39 (HWRNGSEL0), UAD1.45 (SER1W), UAD1.46 (CRCEN), UAD1.50 (DGND), UAD1.51 (REGGNDD), UAD1.58 (OS0), UAD1.59 (OS1), UAD1.60 (OS2), UAD1.61 (BURST), UAD1.64 (CHSEL0), UAD1.65 (CHSEL1), UAD1.66 (CHSEL2), UAD1.69 (REGGND), UAD1.72 (AGND), UAD1.74 (V0BGND), UAD1.76 (V1BGND), UAD1.78 (V2BGND), UAD1.80 (V3BGND), UAD2.1 (V4BGND), UAD2.3 (V5BGND), UAD2.5 (AGND), UAD2.8 (V6BGND), UAD2.10 (V7BGND), UAD2.11 (V7AGND), UAD2.13 (V6AGND), UAD2.16 (AGND), UAD2.18 (V5AGND), UAD2.20 (V4AGND), UAD2.21 (V3AGND), UAD2.23 (V2AGND), UAD2.25 (V1AGND), UAD2.27 (V0AGND), UAD2.29 (AGND), UAD2.32 (REFGND), UAD2.34 (REFINOUTGND), UAD2.35 (REFSEL), UAD2.39 (HWRNGSEL0), UAD2.45 (SER1W), UAD2.46 (CRCEN), UAD2.50 (DGND), UAD2.51 (REGGNDD), UAD2.58 (OS0), UAD2.59 (OS1), UAD2.60 (OS2), UAD2.61 (BURST), UAD2.64 (CHSEL0), UAD2.65 (CHSEL1), UAD2.66 (CHSEL2), UAD2.69 (REGGND), UAD2.72 (AGND), UAD2.74 (V0BGND), UAD2.76 (V1BGND), UAD2.78 (V2BGND), UAD2.80 (V3BGND), UAD3.1 (V4BGND), UAD3.3 (V5BGND), UAD3.5 (AGND), UAD3.8 (V6BGND), UAD3.10 (V7BGND), UAD3.11 (V7AGND), UAD3.13 (V6AGND), UAD3.16 (AGND), UAD3.18 (V5AGND), UAD3.20 (V4AGND), UAD3.21 (V3AGND), UAD3.23 (V2AGND), UAD3.25 (V1AGND), UAD3.27 (V0AGND), UAD3.29 (AGND), UAD3.32 (REFGND), UAD3.34 (REFINOUTGND), UAD3.35 (REFSEL), UAD3.39 (HWRNGSEL0), UAD3.45 (SER1W), UAD3.46 (CRCEN), UAD3.50 (DGND), UAD3.51 (REGGNDD), UAD3.58 (OS0), UAD3.59 (OS1), UAD3.60 (OS2), UAD3.61 (BURST), UAD3.64 (CHSEL0), UAD3.65 (CHSEL1), UAD3.66 (CHSEL2), UAD3.69 (REGGND), UAD3.72 (AGND), UAD3.74 (V0BGND), UAD3.76 (V1BGND), UAD3.78 (V2BGND), UAD3.80 (V3BGND), UT0.11 (V-), UT1.11 (V-), UT2.11 (V-), UT3.11 (V-), UT4.11 (V-), UT5.11 (V-), UT6.11 (V-), UT7.11 (V-), UT8.11 (V-), UT9.11 (V-), UT10.11 (V-), UT11.11 (V-), UT12.11 (V-), UT13.11 (V-), UT14.11 (V-), UT15.11 (V-)
adc_busy: J12.9, UAD0.67 (BUSY)
adc_convst: J12.3, UAD0.68 (CONVST), UAD1.68 (CONVST), UAD2.68 (CONVST), UAD3.68 (CONVST)
adc_cs0: J12.13, UAD0.63 (CS)
adc_cs1: J12.14, UAD1.63 (CS)
adc_cs2: J12.15, UAD2.63 (CS)
adc_cs3: J12.16, UAD3.63 (CS)
adc_miso: J12.7, UAD0.57 (SDOA), UAD1.57 (SDOA), UAD2.57 (SDOA), UAD3.57 (SDOA)
adc_refc0: Cur0.1, UAD0.31 (REFCAP)
adc_refc1: Cur1.1, UAD1.31 (REFCAP)
adc_refc2: Cur2.1, UAD2.31 (REFCAP)
adc_refc3: Cur3.1, UAD3.31 (REFCAP)
adc_refio0: Crio0.1, UAD0.33 (REFINOUT)
adc_refio1: Crio1.1, UAD1.33 (REFINOUT)
adc_refio2: Crio2.1, UAD2.33 (REFINOUT)
adc_refio3: Crio3.1, UAD3.33 (REFINOUT)
adc_resetn: J12.11, UAD0.36 (RESET), UAD1.36 (RESET), UAD2.36 (RESET), UAD3.36 (RESET)
adc_rgc0: Crgc0.1, UAD0.70 (REGCAP)
adc_rgc1: Crgc1.1, UAD1.70 (REGCAP)
adc_rgc2: Crgc2.1, UAD2.70 (REGCAP)
adc_rgc3: Crgc3.1, UAD3.70 (REGCAP)
adc_rgd0: Crgd0.1, UAD0.52 (REGCAPD)
adc_rgd1: Crgd1.1, UAD1.52 (REGCAPD)
adc_rgd2: Crgd2.1, UAD2.52 (REGCAPD)
adc_rgd3: Crgd3.1, UAD3.52 (REGCAPD)
adc_sclk: J12.5, UAD0.62 (SCLK), UAD1.62 (SCLK), UAD2.62 (SCLK), UAD3.62 (SCLK)

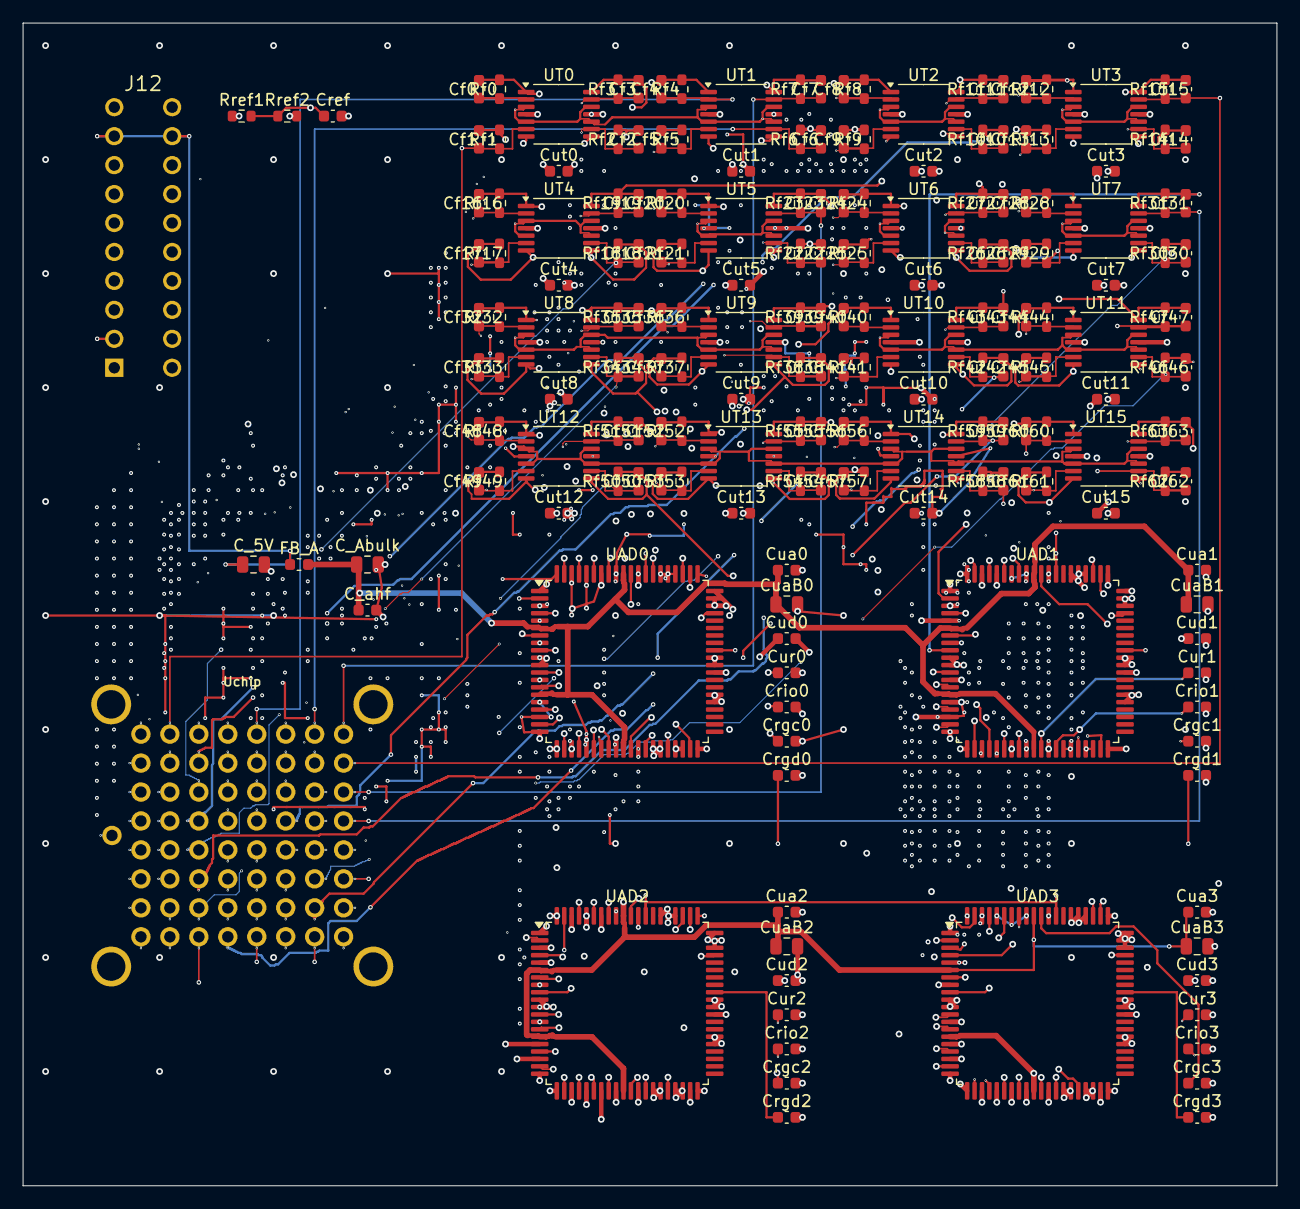
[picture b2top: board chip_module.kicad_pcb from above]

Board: 6 copper layers, 110.0 x 102.0 mm, 201 parts (1 on the bottom side), 158 nets.
